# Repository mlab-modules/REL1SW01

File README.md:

# REL1SW01 - One Relay and/or Two N-MOSFET

## Introduction
The REL1SW01 is a versatile module from the MLAB series designed for triggering high current demaining devices (eg. high power led, high voltage circuits, DC motors, ..) using two N-MOSFET transistors or relay. It supports both bistable and monostable relay configurations and can be integrated into various electronic projects requiring relay switching or direct MOSFET control.

## Features
- Equipped with two N-MOSFET transistors (IRLML6244).
  - Capable of switching voltages up to 20V.
- Supports optional relay addition (e.g., DPDT FRT5).
- Configurable for either relay coil driving or independent transistor switching.
- Compatible with MCU control.

## Specifications
### MOSFET Transistors (IRLML6244)
- **Drain-Source Voltage (Vds):** 20V
- **Gate-Source Voltage (Vgs):** ±12V
- **Continuous Drain Current (Id):** 6.3A
- **Total Power Dissipation (Pd):** 1.3W
- **Gate Threshold Voltage (Vgs(th)):** 1.1V
- **On-State Resistance (Rds(on)):** 21mΩ at Vgs = 4.5V

## Usage
### Without Relay
- Connect the load to the drain of the MOSFET.
- The source of the MOSFET should be connected to GND.
- Use the gate to control switching via the MCU.

### With Relay
- Connect the relay's coil terminals to the MOSFETs as per the required configuration.
- The relay contacts will then be used to switch the external load.

## Configuration
To configure the module for different uses:
1. For direct MOSFET switching, connect the load between the drain and the positive supply (VCC).
2. For relay operation, connect the relay coil to the designated pins controlled by the MOSFETs.

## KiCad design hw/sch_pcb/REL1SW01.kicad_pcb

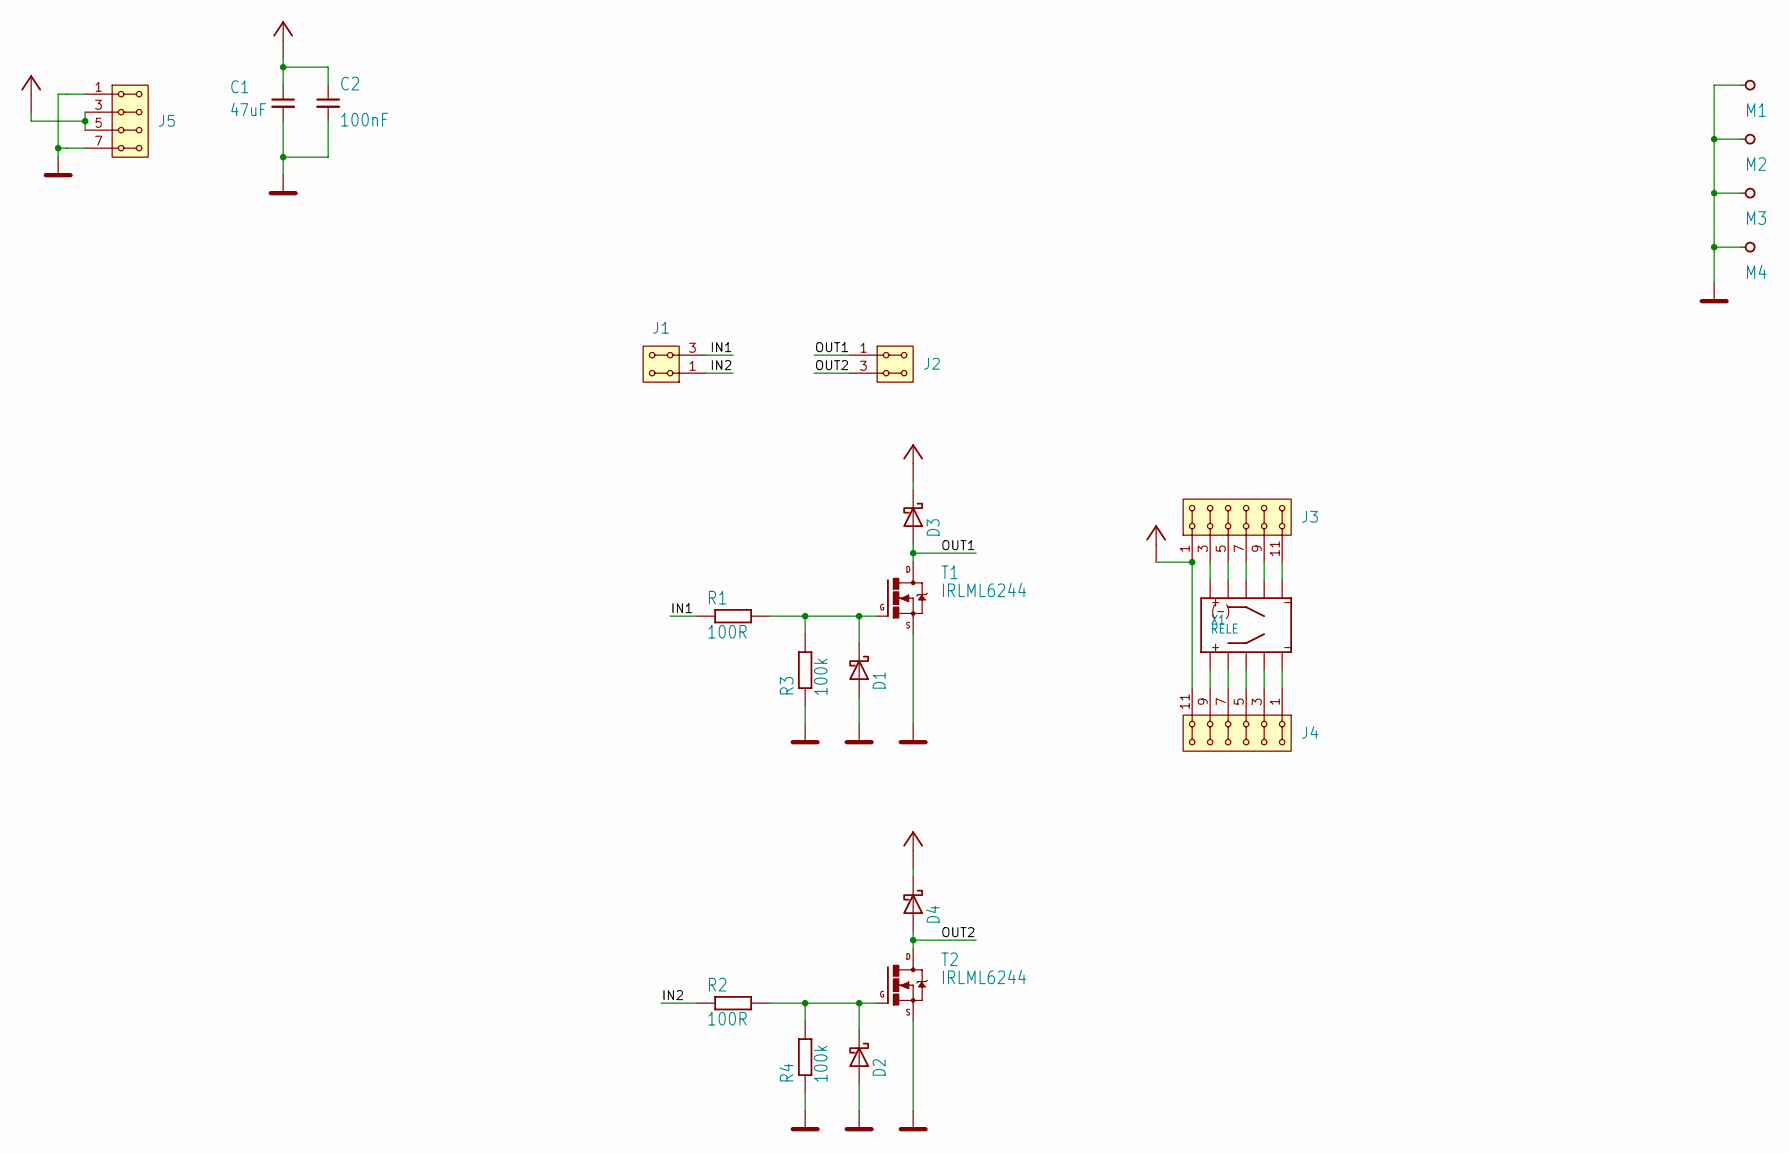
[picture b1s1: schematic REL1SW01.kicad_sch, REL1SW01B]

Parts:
C1: 47uF; C_0805_2012Metric
C2: 100nF; C_0805_2012Metric
D1, D2, D3, D4: SS14; D_SMA
J1, J2: HEADER_2x02_PARALLEL; Straight_2x02
J3, J4: HEADER_2x06_PARALLEL; Straight_2x06
J5: HEADER_2x04_PARALLEL; Straight_2x04
M1, M2, M3, M4: SROUB3M; MountingHole_3mm
R1, R2: 100R; R_0805_2012Metric
R3, R4: 100k; R_0805_2012Metric
T1, T2: IRLML6244; SOT-23
X1: RELE; Relay_DPDT_FRT5

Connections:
+VCC: C1.1, C2.1, D3.1 (K), D4.1 (K), J3.1, J3.2, J4.11, J4.12, J5.3, J5.4, J5.5, J5.6
/IN1: J1.3, J1.4, R1.1
/IN2: J1.1, J1.2, R2.1
/OUT1: D3.2 (A), J2.1, J2.2, T1.3 (D)
/OUT2: D4.2 (A), J2.3, J2.4, T2.3 (D)
GND: C1.2, C2.2, D1.2 (A), D2.2 (A), J5.1, J5.2, J5.7, J5.8, M1.1, M2.1, M3.1, M4.1, R3.1, R4.1, T1.2 (S), T2.2 (S)
unnamed: D1.1 (K), R1.2, R3.2, T1.1 (G)
unnamed: D2.1 (K), R2.2, R4.2, T2.1 (G)
unnamed: J4.9, J4.10, X1.1
unnamed: J4.7, J4.8, X1.2
unnamed: J4.5, J4.6, X1.3
unnamed: J4.3, J4.4, X1.4
unnamed: J4.1, J4.2, X1.5
unnamed: J3.11, J3.12, X1.6
unnamed: J3.9, J3.10, X1.7
unnamed: J3.7, J3.8, X1.8
unnamed: J3.5, J3.6, X1.9
unnamed: J3.3, J3.4, X1.10

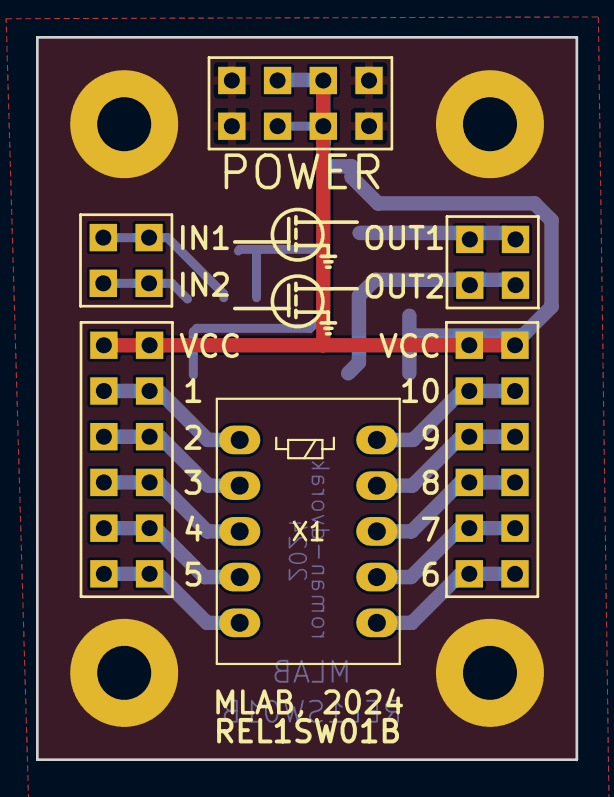
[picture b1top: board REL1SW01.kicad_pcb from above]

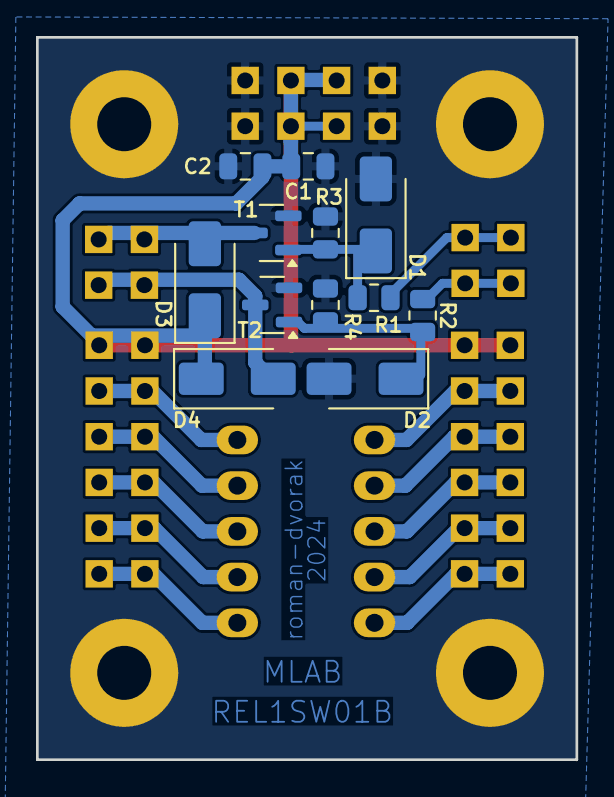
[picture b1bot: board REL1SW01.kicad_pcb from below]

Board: 2 copper layers, 30.0 x 40.1 mm, 22 parts (12 on the bottom side), 18 nets.

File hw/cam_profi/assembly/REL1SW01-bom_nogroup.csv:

Component,Description,Part,References,Value,Footprint,Quantity Per PCB,Datasheet
1,"Unpolarized capacitor, small symbol",C_Small,C2,100nF,C_0805_2012Metric,1,~
2,"Unpolarized capacitor, small symbol",C_Small,C1,47uF,C_0805_2012Metric,1,~
3,"40V 1A Schottky Diode, SMA",SS14,D1D2D3D4,SS14,D_SMA,4,https://www.vishay.com/docs/88746/ss12.pdf
4,"2x02 2.54 mm pitch header, 2 pins next to each other are connected",HEADER_2x02_PARALLEL,J1J2,HEADER_2x02_PARALLEL,Straight_2x02,2,
5,"2x04 2.54 mm pitch header, 2 pins next to each other are connected",HEADER_2x04_PARALLEL,J5,HEADER_2x04_PARALLEL,Straight_2x04,1,
6,"2x06 2.54 mm pitch header, 2 pins next to each other are connected",HEADER_2x06_PARALLEL,J3J4,HEADER_2x06_PARALLEL,Straight_2x06,2,
7,,R0805,R1R2,100R,R_0805_2012Metric,2,
8,,R0805,R3R4,100k,R_0805_2012Metric,2,
9,,IRLML6244TRPBF,T1T2,IRLML6244,SOT-23,2,
10,,RELE,X1,RELE,Relay_DPDT_FRT5,1,

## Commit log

2023-04-01 Adding force option to enable splitting in not fresh copy of Modules repository.
2023-09-17 automated commit; add github actions
2023-09-17 Update workflow files
2023-09-17 Update metadata files
2024-05-14 Update metadata. Remove unused files.
2024-06-02 Transfer to kicad
2024-06-02 Update actions products
2024-06-02 update template
2024-06-02 layout improvements
2024-06-06 Use relative path to title blocks.
2024-07-09 add ust id
